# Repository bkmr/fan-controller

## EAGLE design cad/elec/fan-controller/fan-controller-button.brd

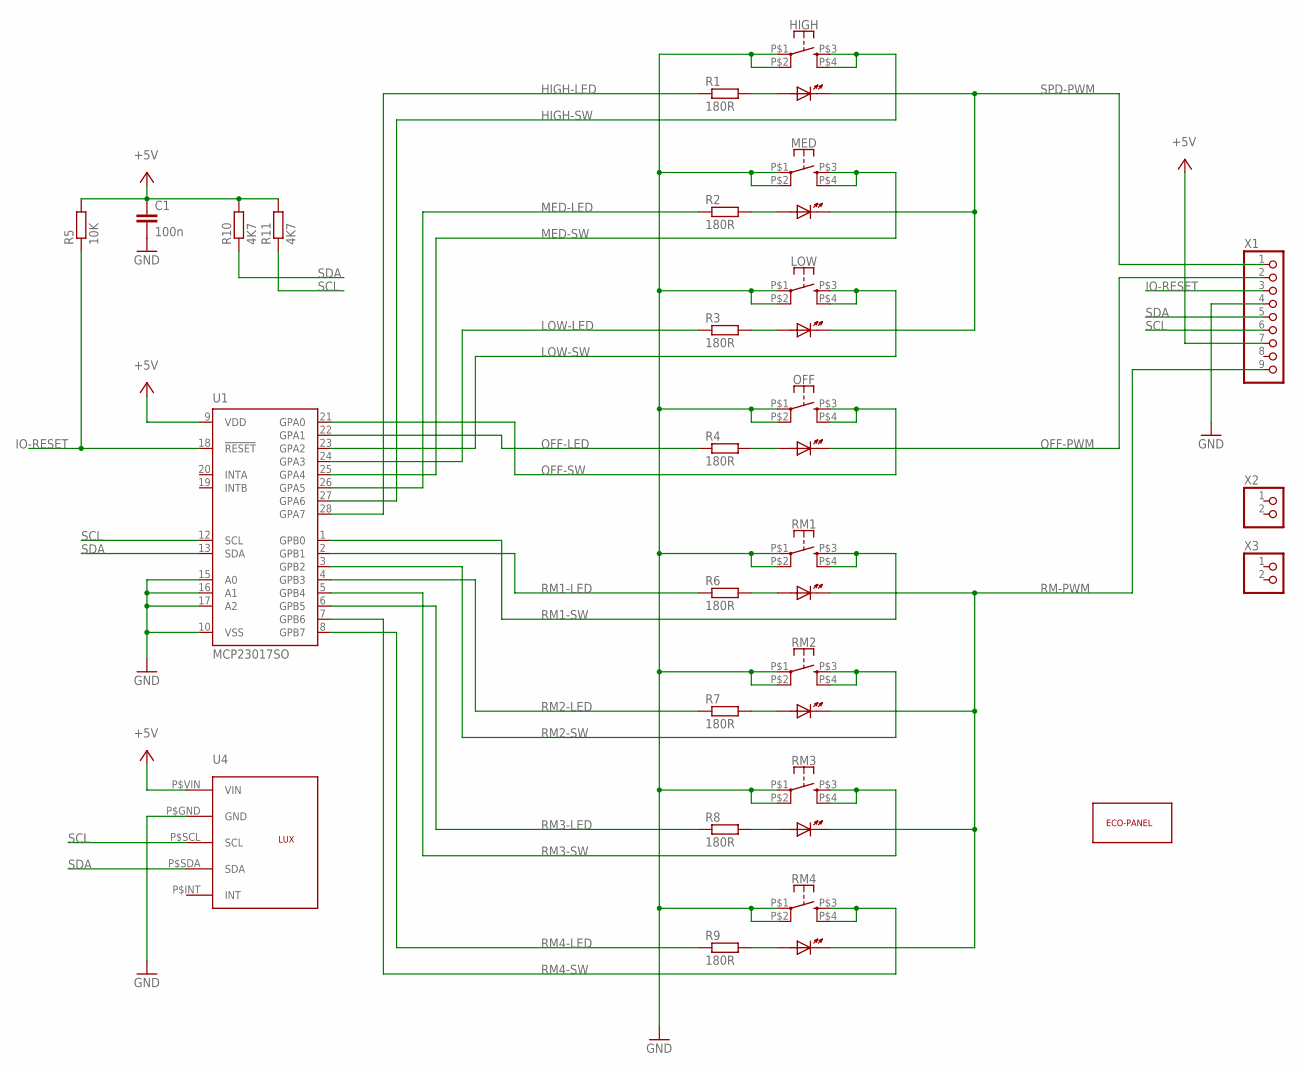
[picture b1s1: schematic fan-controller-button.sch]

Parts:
C1: 100n; C1206
HIGH: JAYCAR-TACTILE-SWITCH-LED; JAYCAR-TACTILE-SWITCH-WITH-LED
LOW: JAYCAR-TACTILE-SWITCH-LED; JAYCAR-TACTILE-SWITCH-WITH-LED
MED: JAYCAR-TACTILE-SWITCH-LED; JAYCAR-TACTILE-SWITCH-WITH-LED
OFF: JAYCAR-TACTILE-SWITCH-LED; JAYCAR-TACTILE-SWITCH-WITH-LED
R1, R2, R3, R4, R6, R7, R8, R9: 180R; M1206
R5: 10K; M0805
R10, R11: 4K7; M0805
RM1, RM2, RM3, RM4: JAYCAR-TACTILE-SWITCH-LED; JAYCAR-TACTILE-SWITCH-WITH-LED
U1: MCP23017SO; SO28W
U4: TSL2561
U$1: ECO-PANEL
X1: PINHD-1X9; 1X09
X2, X3: PINHD-1X2; 1X02

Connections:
+5V: C1.1, R5.2, R10.2, R11.2, U1.9 (VDD), U4.P$VIN (VIN), X1.7
GND: C1.2, HIGH.P$1 (1), HIGH.P$2 (2), LOW.P$1 (1), LOW.P$2 (2), MED.P$1 (1), MED.P$2 (2), OFF.P$1 (1), OFF.P$2 (2), RM1.P$1 (1), RM1.P$2 (2), RM2.P$1 (1), RM2.P$2 (2), RM3.P$1 (1), RM3.P$2 (2), RM4.P$1 (1), RM4.P$2 (2), U1.10 (VSS), U1.15 (A0), U1.16 (A1), U1.17 (A2), U4.P$GND (GND), X1.4
HIGH-LED: R1.1, U1.28 (GPA7)
HIGH-SW: HIGH.P$3 (3), HIGH.P$4 (4), U1.27 (GPA6)
IO-RESET: R5.1, U1.18 (!RESET), X1.3
LOW-LED: R3.1, U1.24 (GPA3)
LOW-SW: LOW.P$3 (3), LOW.P$4 (4), U1.23 (GPA2)
MED-LED: R2.1, U1.26 (GPA5)
MED-SW: MED.P$3 (3), MED.P$4 (4), U1.25 (GPA4)
unnamed: HIGH.P$A (A), R1.2
unnamed: MED.P$A (A), R2.2
unnamed: LOW.P$A (A), R3.2
unnamed: OFF.P$A (A), R4.2
unnamed: R6.2, RM1.P$A (A)
unnamed: R7.2, RM2.P$A (A)
unnamed: R8.2, RM3.P$A (A)
unnamed: R9.2, RM4.P$A (A)
OFF-LED: R4.1, U1.22 (GPA1)
OFF-PWM: OFF.P$K (K), X1.2
OFF-SW: OFF.P$3 (3), OFF.P$4 (4), U1.21 (GPA0)
RM1-LED: R6.1, U1.2 (GPB1)
RM1-SW: RM1.P$3 (3), RM1.P$4 (4), U1.1 (GPB0)
RM2-LED: R7.1, U1.4 (GPB3)
RM2-SW: RM2.P$3 (3), RM2.P$4 (4), U1.3 (GPB2)
RM3-LED: R8.1, U1.6 (GPB5)
RM3-SW: RM3.P$3 (3), RM3.P$4 (4), U1.5 (GPB4)
RM4-LED: R9.1, U1.8 (GPB7)
RM4-SW: RM4.P$3 (3), RM4.P$4 (4), U1.7 (GPB6)
RM-PWM: RM1.P$K (K), RM2.P$K (K), RM3.P$K (K), RM4.P$K (K), X1.9
SCL: R11.1, U1.12 (SCL), U4.P$SCL (SCL), X1.6
SDA: R10.1, U1.13 (SDA), U4.P$SDA (SDA), X1.5
SPD-PWM: HIGH.P$K (K), LOW.P$K (K), MED.P$K (K), X1.1

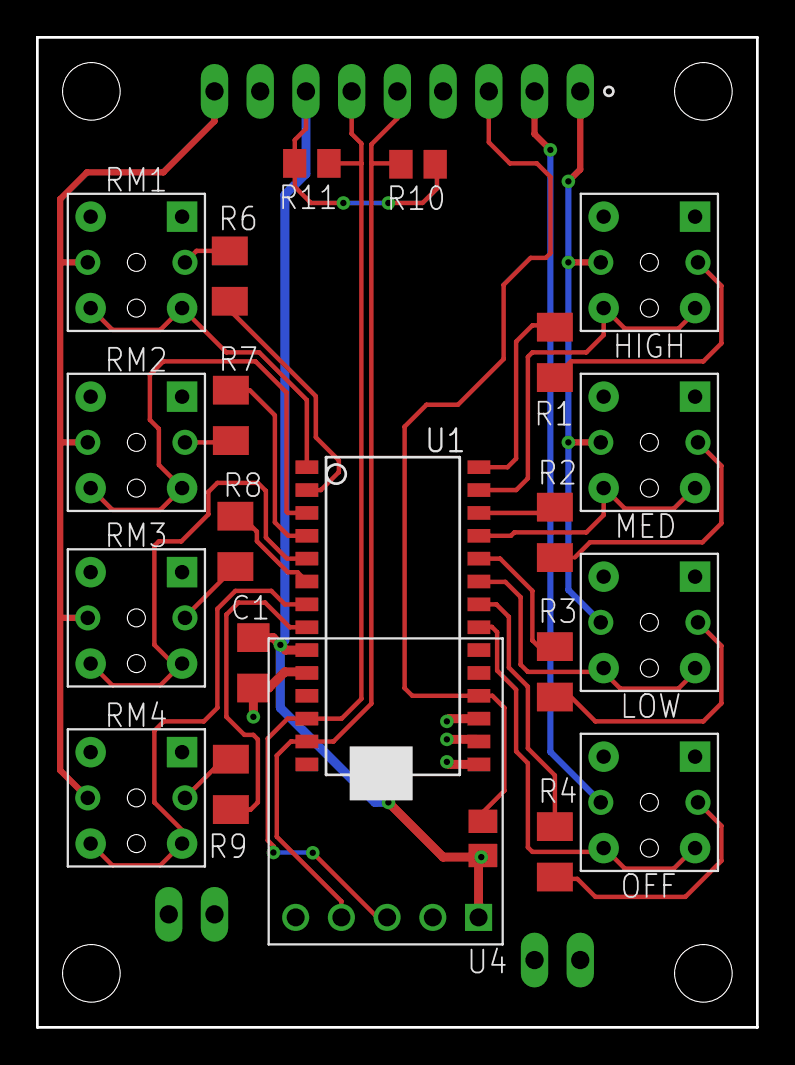
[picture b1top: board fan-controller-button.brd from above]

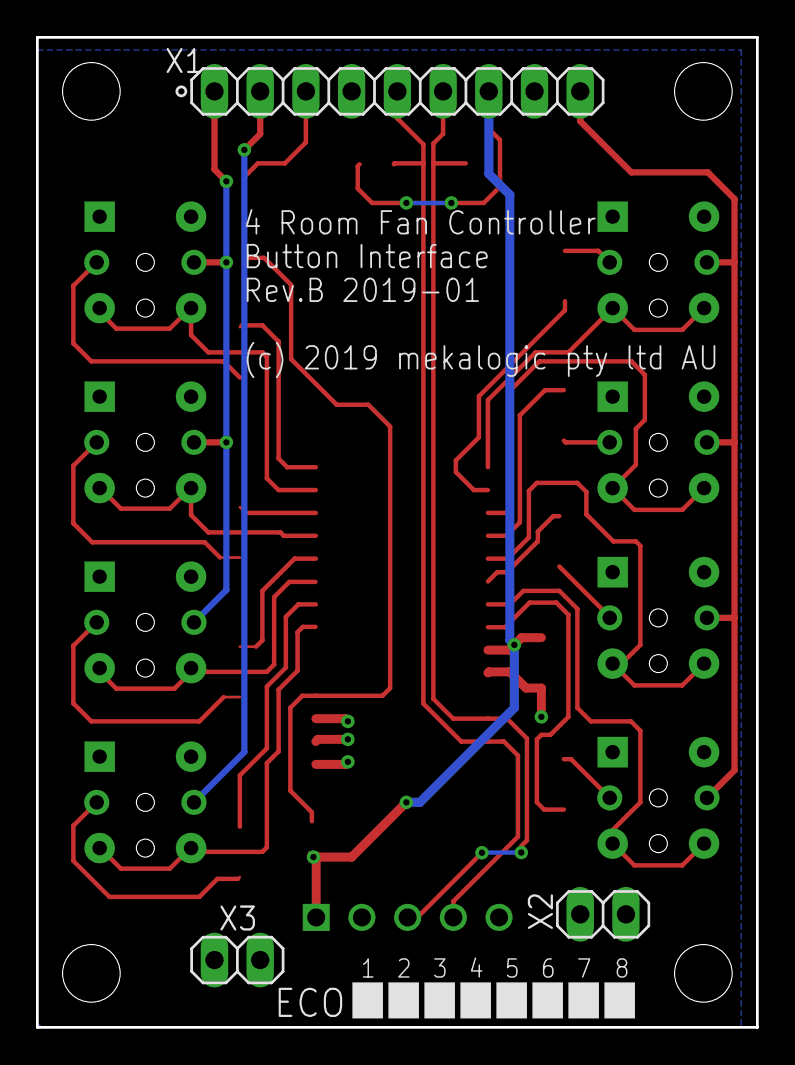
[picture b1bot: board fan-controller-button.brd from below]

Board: 2 copper layers, 40.0 x 55.0 mm, 26 parts (4 on the bottom side), 32 nets.

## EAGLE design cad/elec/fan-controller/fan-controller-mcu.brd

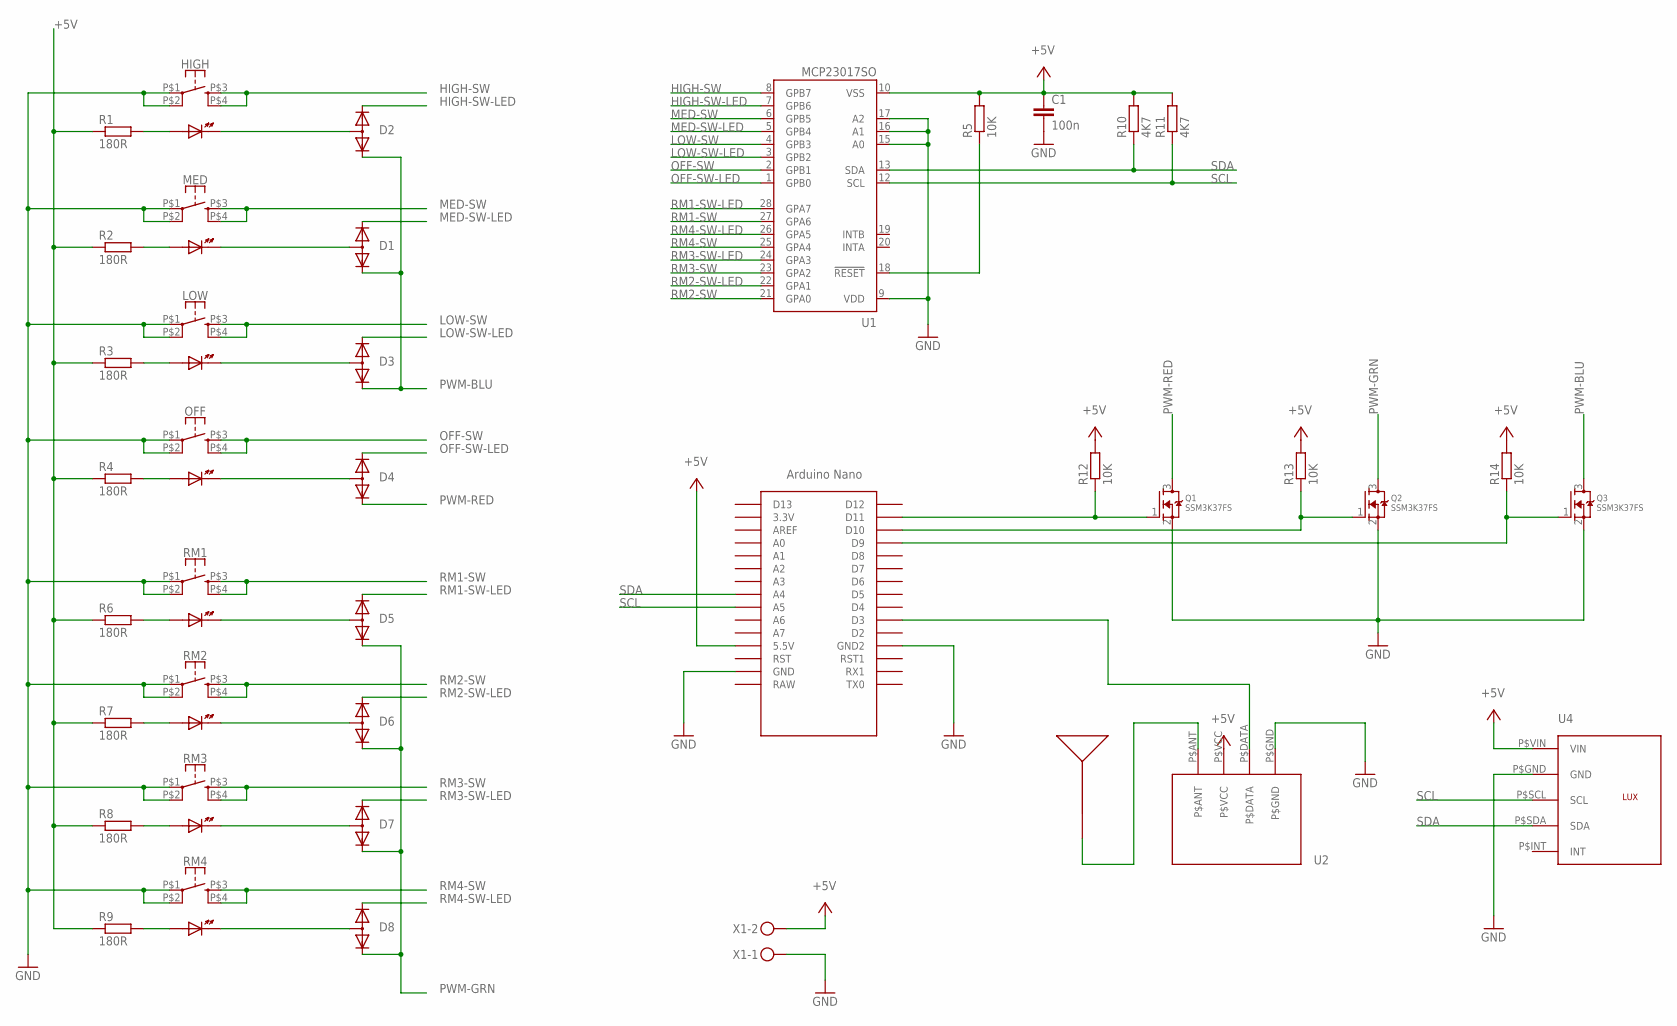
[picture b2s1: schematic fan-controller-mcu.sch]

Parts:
C1: 100n; C1206
D1, D2, D3, D4, D5, D6, D7, D8: BAW56-7-F; SOT23; DIGIKEY BAW56-FDICT-ND
HIGH: JAYCAR-TACTILE-SWITCH-LED; JAYCAR-TACTILE-SWITCH-WITH-LED
LOW: JAYCAR-TACTILE-SWITCH-LED; JAYCAR-TACTILE-SWITCH-WITH-LED
MED: JAYCAR-TACTILE-SWITCH-LED; JAYCAR-TACTILE-SWITCH-WITH-LED
OFF: JAYCAR-TACTILE-SWITCH-LED; JAYCAR-TACTILE-SWITCH-WITH-LED
Q1, Q2, Q3: SSM3K37FS; SOT23; DIGIKEY SSM3K37FSLFCT-ND
R1, R2, R3, R4, R6, R7, R8, R9: 180R; M1206
R5, R12, R13, R14: 10K; M0805
R10, R11: 4K7; M0805
RM1, RM2, RM3, RM4: JAYCAR-TACTILE-SWITCH-LED; JAYCAR-TACTILE-SWITCH-WITH-LED
U1: MCP23017SO; SO28W
U2: 433-TX
U3: NANO
U4: TSL2561
U$2: ANTENNA
X1: MKDSN1,5/2-5,08

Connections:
+5V: C1.1, R1.1, R2.1, R3.1, R4.1, R5.2, R6.1, R7.1, R8.1, R9.1, R10.2, R11.2, R12.2, R13.2, R14.2, U1.10 (VSS), U2.P$VCC, U3.5V (5.5V), U4.P$VIN (VIN), X1.2
GND: C1.2, HIGH.P$1 (1), HIGH.P$2 (2), LOW.P$1 (1), LOW.P$2 (2), MED.P$1 (1), MED.P$2 (2), OFF.P$1 (1), OFF.P$2 (2), Q1.2 (S), Q2.2 (S), Q3.2 (S), RM1.P$1 (1), RM1.P$2 (2), RM2.P$1 (1), RM2.P$2 (2), RM3.P$1 (1), RM3.P$2 (2), RM4.P$1 (1), RM4.P$2 (2), U1.9 (VDD), U1.15 (A0), U1.16 (A1), U1.17 (A2), U2.P$GND, U3.GND, U3.GND1 (GND2), U4.P$GND (GND), X1.1
HIGH-SW: HIGH.P$3 (3), HIGH.P$4 (4), U1.8 (GPB7)
HIGH-SW-LED: D2.2 (K2), U1.7 (GPB6)
LOW-SW: LOW.P$3 (3), LOW.P$4 (4), U1.4 (GPB3)
LOW-SW-LED: D3.2 (K2), U1.3 (GPB2)
MED-SW: MED.P$3 (3), MED.P$4 (4), U1.6 (GPB5)
MED-SW-LED: D1.2 (K2), U1.5 (GPB4)
unnamed: D2.3 (A), HIGH.P$K (K)
unnamed: Q1.1 (G), R12.1, U3.D11
unnamed: D1.3 (A), MED.P$K (K)
unnamed: Q2.1 (G), R13.1, U3.D10
unnamed: HIGH.P$A (A), R1.2
unnamed: MED.P$A (A), R2.2
unnamed: D3.3 (A), LOW.P$K (K)
unnamed: Q3.1 (G), R14.1, U3.D9
unnamed: LOW.P$A (A), R3.2
unnamed: D4.3 (A), OFF.P$K (K)
unnamed: U2.P$DATA, U3.D3
unnamed: OFF.P$A (A), R4.2
unnamed: R5.1, U1.18 (!RESET)
unnamed: D5.3 (A), RM1.P$K (K)
unnamed: U2.P$ANT, U$2.P$1
unnamed: R6.2, RM1.P$A (A)
unnamed: D6.3 (A), RM2.P$K (K)
unnamed: R7.2, RM2.P$A (A)
unnamed: D7.3 (A), RM3.P$K (K)
unnamed: R8.2, RM3.P$A (A)
unnamed: D8.3 (A), RM4.P$K (K)
unnamed: R9.2, RM4.P$A (A)
OFF-SW: OFF.P$3 (3), OFF.P$4 (4), U1.2 (GPB1)
OFF-SW-LED: D4.2 (K2), U1.1 (GPB0)
PWM-BLU: D1.1 (K1), D2.1 (K1), D3.1 (K1), Q3.3 (D)
PWM-GRN: D5.1 (K1), D6.1 (K1), D7.1 (K1), D8.1 (K1), Q2.3 (D)
PWM-RED: D4.1 (K1), Q1.3 (D)
RM1-SW: RM1.P$3 (3), RM1.P$4 (4), U1.27 (GPA6)
RM1-SW-LED: D5.2 (K2), U1.28 (GPA7)
RM2-SW: RM2.P$3 (3), RM2.P$4 (4), U1.21 (GPA0)
RM2-SW-LED: D6.2 (K2), U1.22 (GPA1)
RM3-SW: RM3.P$3 (3), RM3.P$4 (4), U1.23 (GPA2)
RM3-SW-LED: D7.2 (K2), U1.24 (GPA3)
RM4-SW: RM4.P$3 (3), RM4.P$4 (4), U1.25 (GPA4)
RM4-SW-LED: D8.2 (K2), U1.26 (GPA5)
SCL: R11.1, U1.12 (SCL), U3.A5, U4.P$SCL (SCL)
SDA: R10.1, U1.13 (SDA), U3.A4, U4.P$SDA (SDA)

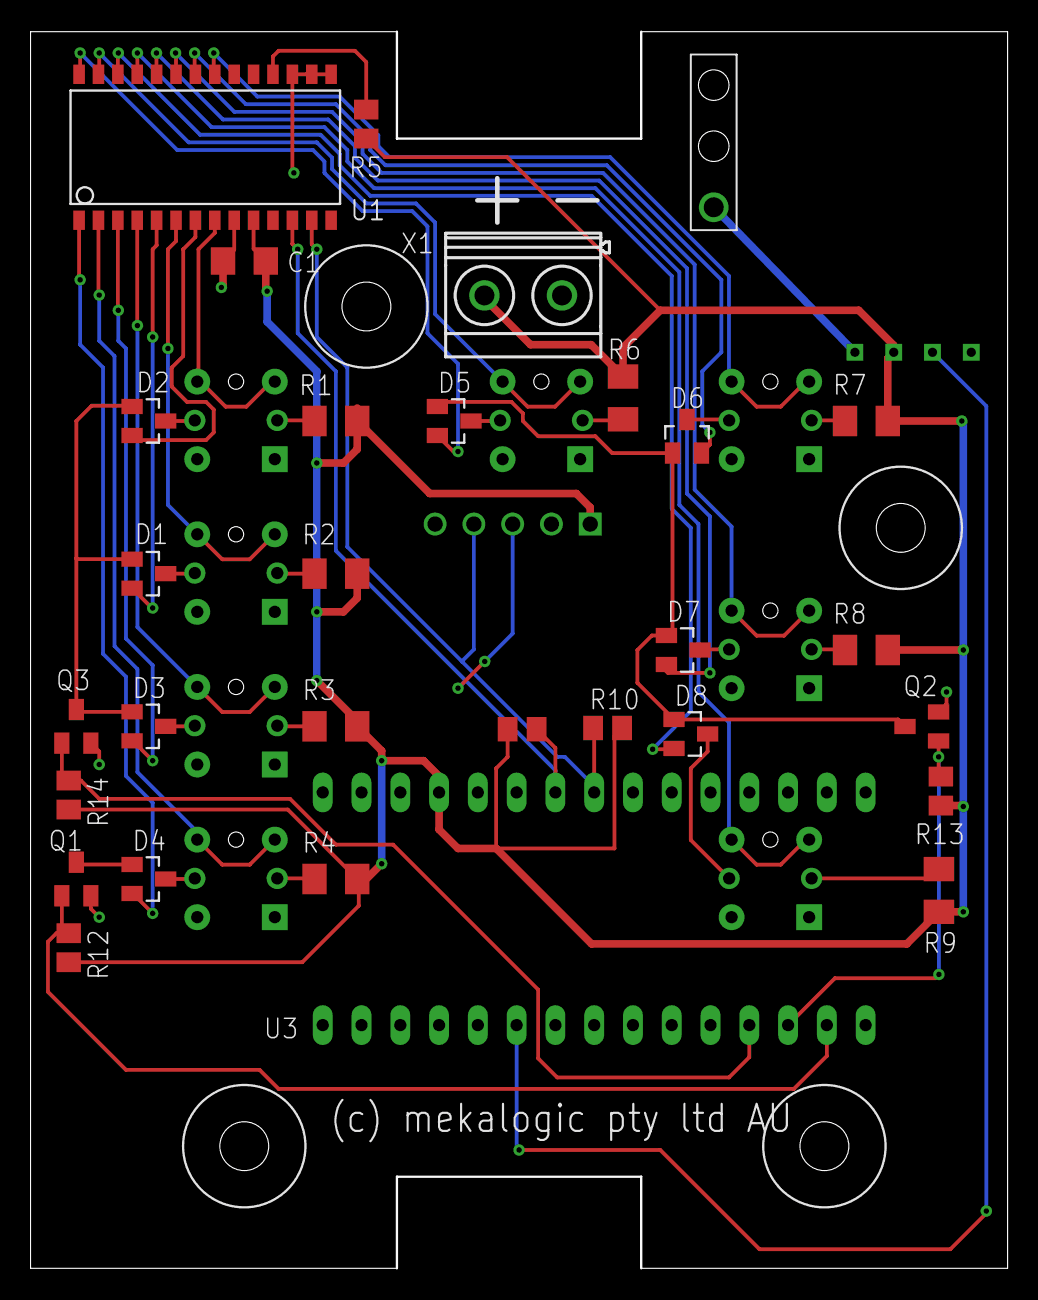
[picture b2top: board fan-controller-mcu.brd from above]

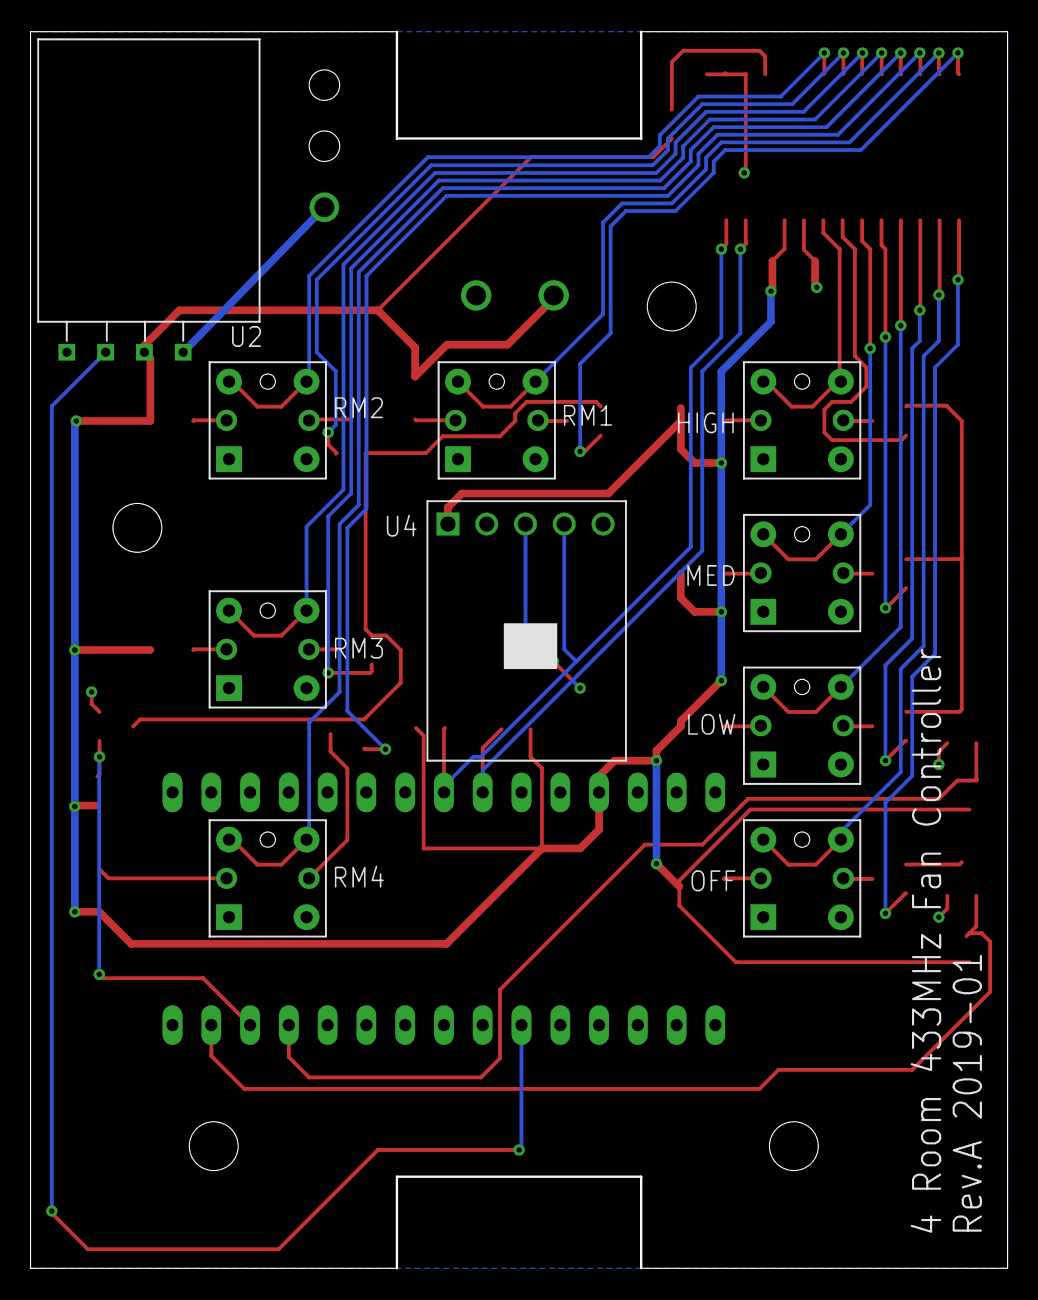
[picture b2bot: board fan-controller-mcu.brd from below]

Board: 2 copper layers, 64.0 x 81.0 mm, 40 parts (10 on the bottom side), 45 nets.

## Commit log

2018-12-17 Added more generic command craetion capability
2018-12-20 Added all four bedrooms and tested
2019-01-08 Test with MCP23017 IO Expander and LED PWM/diode combinantion
2019-01-08 Added initial electrical PCB layout and schematic
    -need to investigate 2 PCB solution
2019-01-10 Updated so that buttons do not include 433 MHz transmitter or MCU
    -made button layout generic
    -moved IO Expander to button board
    -added ECO panel
    -generated Rev.A outputs
2019-01-14 Added 2x2 pin mounting pin headers on 2.54 mm pitch
    -allows perf board to be mounted directly and securely to buttton board
2019-01-30 Added new classes to support IO Expander LEDs and Switches
2019-02-11 clean up
2019-02-13 Removed artificial constraint that you could not send the same command twice
    -fixes bug with sending the same command to different rooms
    -added notify LED to confirm RF operation for debugging

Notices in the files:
cad/elec/fan-controller/fan-controller-button.brd:
(c) 2019 mekalogic pty ltd AU
